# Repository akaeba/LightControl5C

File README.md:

# LightControl5C

Five microcontroller controlled output stages with an integrated voltage selectable power supply.

## Features
* five free programmable outputs
* up to 500mA per output (all 600mA max)
* voltage divider selectable output voltage
* optimized for 24V input voltage
* up to 20V output voltage
* inductive load capable
* ICSP programming interface
* 44mm x 27mm overall size

## Pinning
| Port     | Usage                                                             |
| -------- | ----------------------------------------------------------------- |
| X1       | positive input supply, max. 28V, DC-only                          |
| X2       | negative input supply (GND)                                       |
| X3       | ICSP programming                                                  |
| X4       | GND                                                               |
| X5       | open-drain uC output (GP0)                                        |
| X6       | open-drain uC output (GP1)                                        |
| X7       | open-drain uC output (GP2)                                        |
| X8       | open-drain uC output (GP4)                                        |
| X9       | open-drain uC output (GP5)                                        |
| X10, X11 | positive supply for X5-X9, voltage via R<sub>FBT</sub> adjustable |

## How to build
* Get your PCB:
  - [Aisler](https://aisler.net/p/RHHJMNNA)
  - [PCBway](https://www.pcbway.com/project/shareproject/LightControl5C_13ccc4e5.html)
* Order Components from:
  - [Reichelt](/bom/LightControl5C_Reichelt.csv)
  - [Mouser](/bom/LightControl5C_Mouser.csv)

## Gallery
<tr>
<td>  </td>
<td>  </td>
<td>  </td>
</tr>

## Tooling
* PCB and schematic: [Eagle 7.7](http://eagle.autodesk.com/eagle/software-versions/1)
* Compiler: [MikroC Pro for PIC 7.1](https://download.mikroe.com/setups/compilers/mikroc/pic/mikroc-pic-setup-v710.zip)
* Programmer:
  - [PicKit2 HW](https://www.microchip.com/en-us/development-tool/pg164120) - check also the clone vendors ;-)
  - [PicKit2 SW](https://ww1.microchip.com/downloads/aemDocuments/documents/OTH/ProductDocuments/SoftwareLibraries/Firmware/PICkit2v2.61.00SetupA.zip)

## References
* [LV3842: 4-V to 36-V, 600-mA, Synchronous Step-Down Converter](https://www.ti.com/lit/ds/symlink/lv3842.pdf)
* [PIC12F675: 8-Pin, Flash-Based 8-Bit CMOS Microcontrollers](https://ww1.microchip.com/downloads/aemDocuments/documents/MCU08/ProductDocuments/DataSheets/41190G.pdf)
* [ULN2003: Seven Darlington arrays](https://www.st.com/resource/en/datasheet/uln2003.pdf)
* [TPL7407LA:  30V 7-Channel Low Side Driver](https://www.ti.com/lit/ds/symlink/tpl7407la.pdf)

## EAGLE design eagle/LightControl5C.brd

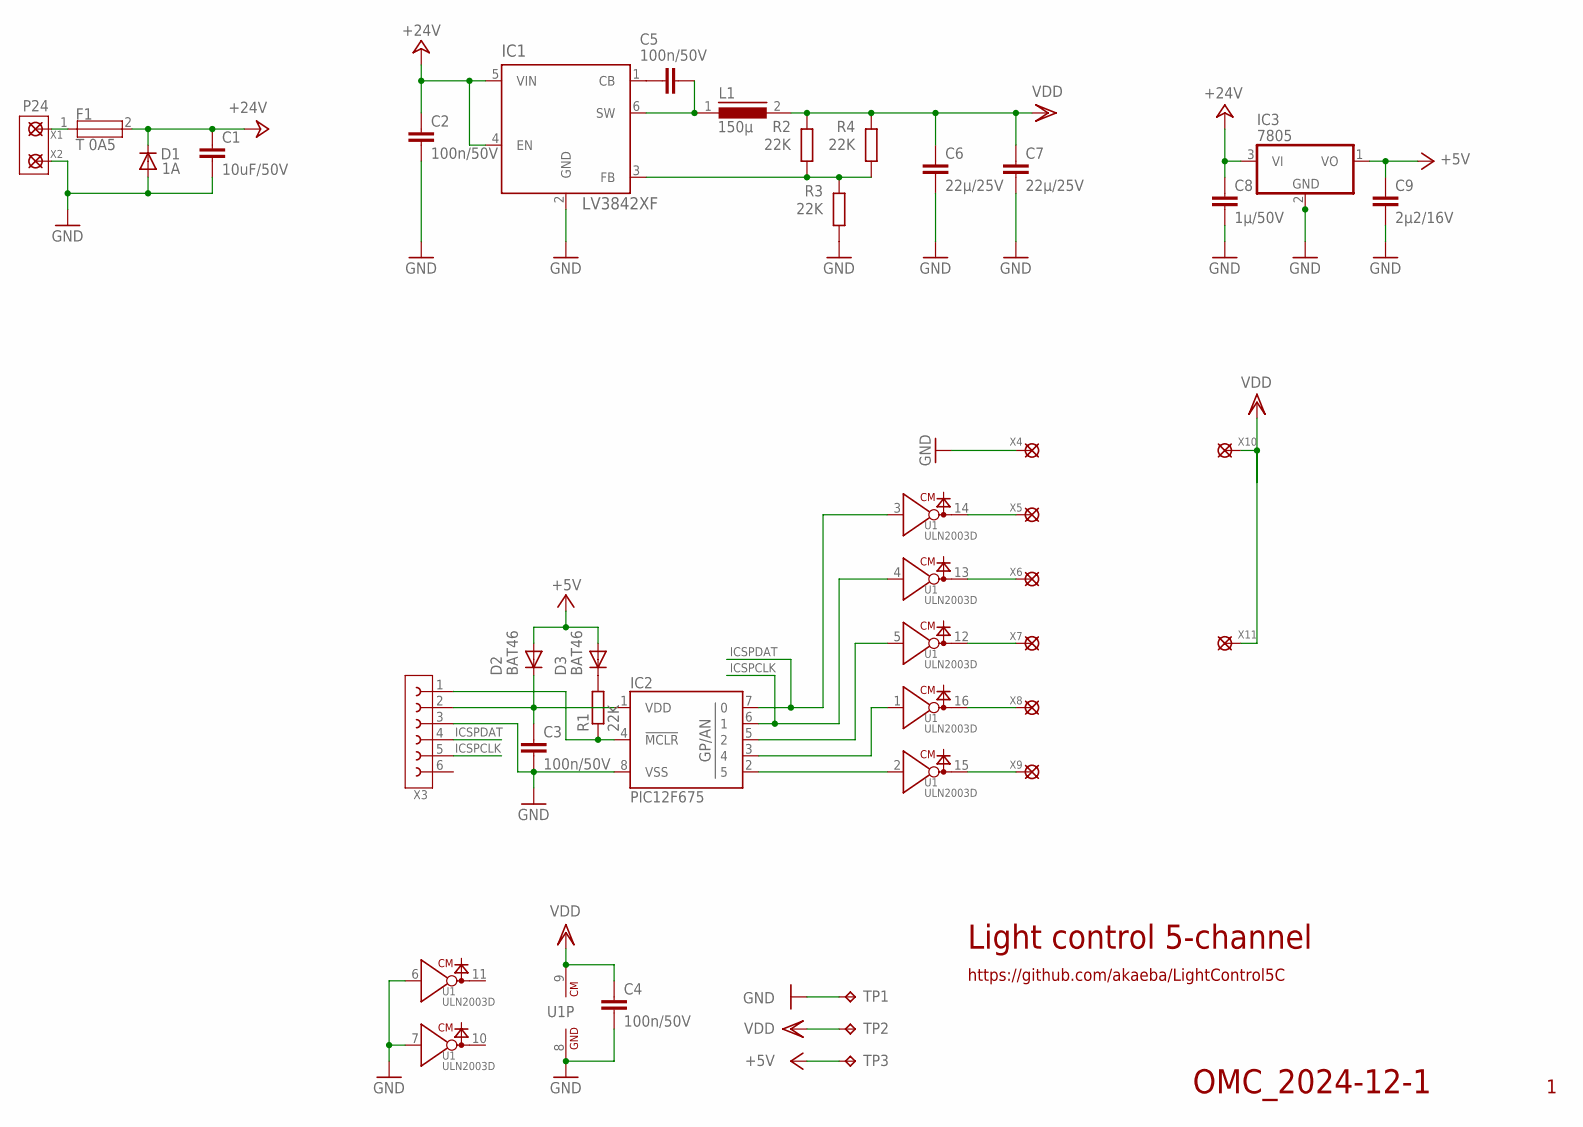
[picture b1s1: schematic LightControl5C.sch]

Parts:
C1: 10uF/50V; C2220K
C2, C3, C4, C5: 100n/50V; 0805
C6, C7: 22µ/25V; 1210
C8: 1µ/50V; 0805
C9: 2µ2/16V; 0805
D1: 1A; DO214AC
D2, D3: BAT46; SOD123
F1: T 0A5; OMT125
IC1: LV3842XF; SOT23-6
IC2: PIC12F675; SOIC08
IC3: 7805; SOT89W
L1: 150µ; PISM
R1, R2, R3, R4: 22K; 0805
TP1, TP2, TP3: TPB1,27; B1,27
U1: ULN2003D; SOIC16
X1, X2, X4, X5, X6, X7, X8, X9, X10, X11: Footprint; L38W19X1
X3: FLE-103-01; FLE-103

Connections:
+5V: C9.1, D2.A, D3.A, IC3.1 (VO), TP3.TP
+24V: C1.1, C2.1, C8.1, D1.C, F1.2, IC1.4 (EN), IC1.5 (VIN), IC3.3 (VI)
GND: C1.2, C2.2, C3.2, C4.2, C6.2, C7.2, C8.2, C9.2, D1.A, IC1.2 (GND), IC2.8 (VSS), IC3.2 (GND), IC3.4 (GND), R3.1, TP1.TP, U1.6 (IN), U1.7 (IN), U1.8 (GND), X2.1, X3.3, X4.1
ICSPCLK: IC2.6 (1), U1.4 (IN), X3.5
ICSPDAT: IC2.7 (0), U1.3 (IN), X3.4
unnamed: IC1.3 (FB), R2.1, R3.2, R4.1
unnamed: D3.C, R1.2
unnamed: C3.1, D2.C, IC2.1 (VDD), X3.2
unnamed: IC2.4 (!MCLR!), R1.1, X3.1
unnamed: C5.1, IC1.1 (CB)
unnamed: U1.15 (OUT), X9.1
unnamed: U1.14 (OUT), X5.1
unnamed: IC2.5 (2), U1.5 (IN)
unnamed: IC2.3 (4), U1.1 (IN)
unnamed: IC2.2 (5), U1.2 (IN)
unnamed: U1.13 (OUT), X6.1
unnamed: U1.12 (OUT), X7.1
unnamed: U1.16 (OUT), X8.1
N$SWT: C5.2, IC1.6 (SW), L1.1
P24: F1.1, X1.1
VDD: C4.1, C6.1, C7.1, L1.2, R2.2, R4.2, TP2.TP, U1.9 (CM+), X10.1, X11.1

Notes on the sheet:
Light control 5-channel
https://github.com/akaeba/LightControl5C
OMC_2024-12-1

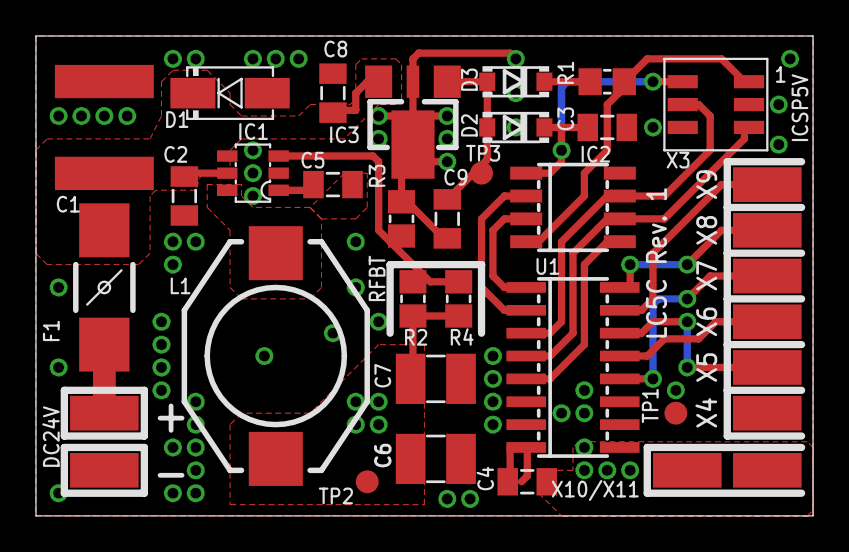
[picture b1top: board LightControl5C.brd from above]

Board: 2 copper layers, 43.2 x 26.7 mm, 36 parts (0 on the bottom side), 21 nets.

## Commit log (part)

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2024-12-09 add gitignore
2024-12-09 PCB Cad files
2024-12-09 add schematic
2024-12-09 [bom] reichelt components
2024-12-09 [bom] partlist reichelt revised
2024-12-09 [bom] mouser partlist
2024-12-09 [bom] general partlist
2024-12-09 [pdf] component placement
2024-12-09 README.md
2024-12-09 [mouser] use csv instead of xls list
2024-12-09 [doc] minor updates on README.md
2024-12-10 [doc] add some pics
2024-12-10 [doc] add some pics to readme
2024-12-10 [doc]: add picture to gallery
2024-12-10 [doc] correct link to pic
2024-12-11 add output voltage
2024-12-12 [doc] add tooling section
2024-12-12 [README.md] add link to PicKit2 SW
2024-12-15 [eagle] add comment for Vmax for L of 22u
2024-12-18 [doc] add link to PCBway
2024-12-19 [bom] now as excel sheet
2024-12-19 [gerber] add gerber files from board
2024-12-19 [gerber] update files
2024-12-21 [gitignore] MikroC Pro for Pic
2024-12-21 [fw] add example project of running leds
2024-12-21 [doc] add link to ULN2003 FET alternative
2026-06-13 [pdf] schematic
    -> update derived docs
2026-06-13 [eagle] change inductor
    -> increase min. inductor size to allow lower currents
2026-06-13 [fw] rename MikroC example
2026-06-13 [fw/MikroC] rename to match with MPLAB X
2026-06-13 [fw/MplabX] add MikroC beloging project
2026-06-13 [gitignore] remove some blank lines

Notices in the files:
parts and their libraries:
omcCapacitor: Copyright & License
This library is licensed under the General Public License, Version 2.
More Information about the General Public License is available at http://www.gnu.org/copyleft/gpl.html.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
omcDiode: This library is licensed under the General Public License, Version 3.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
